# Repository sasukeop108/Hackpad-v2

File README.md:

# Hackpad-v2

Hii! This is a hackpad with 16 keys, 15 sk6812-e mini leds, a xiao rp2040 devolopment board and 16 zener diode 1n4148 with a case made using the fusion 360 software with a lid . It uses the 4*4 matrix to use less pins . The pcb was designed using the help of the pcb  software kicad. This is really basic hardware project and i have built this before but im building this once again with more keys to get back on hardware as i havent shipped any hardware project for months. It is made using the hackpad.hackclub.com guide Made for the event embassy.hackclub.com . It uses circuit python and kmk softwares.

## Schematics

## PCB

## Assembly

 ## Lid

## Case

## BOM
|Quantity|Name         |price            |purpose                       |
|--------|-------------|-----------------|------------------------------|
|1       |Xiao rp2040  |already available|for microcontrolling          |
|16      |cherry mx    |already available|the keys                      |
|16      |sk6812 mini-e|already available|rgb lights which keep changing|
|16      |blank keycaps|already available|to identify key               |
|16      |1n4148 diode |already available|to prevent ghosting of current|
|4       |M3 screws    |already available|to mount case                 |

## Building guide

First, solder the smaller components like the diodes and the sk6812 mini-e led. Then solder components like the rp2040 and switches. Download circuit python in your rp2040 and export the firmware.py code in your rp2040 storage. Assemble it in the 3d printed case available in /CAD folder. Woah! Your now good to go with a hackpad.

## Sourcing guide

Download the gerber file in the repo, paste it in any pcb fabrication service page and order your pcb! You could even change anything using the kicad files and this is fully opensource!.

## AI usage disclosure
Used AI to debug the error cause of which i was unable to push readme from vscode to repo and made it fix the issue

## Credits
- embassy.hackclub.com
- Hackpad.hackclub.com
- www.hackclub.com

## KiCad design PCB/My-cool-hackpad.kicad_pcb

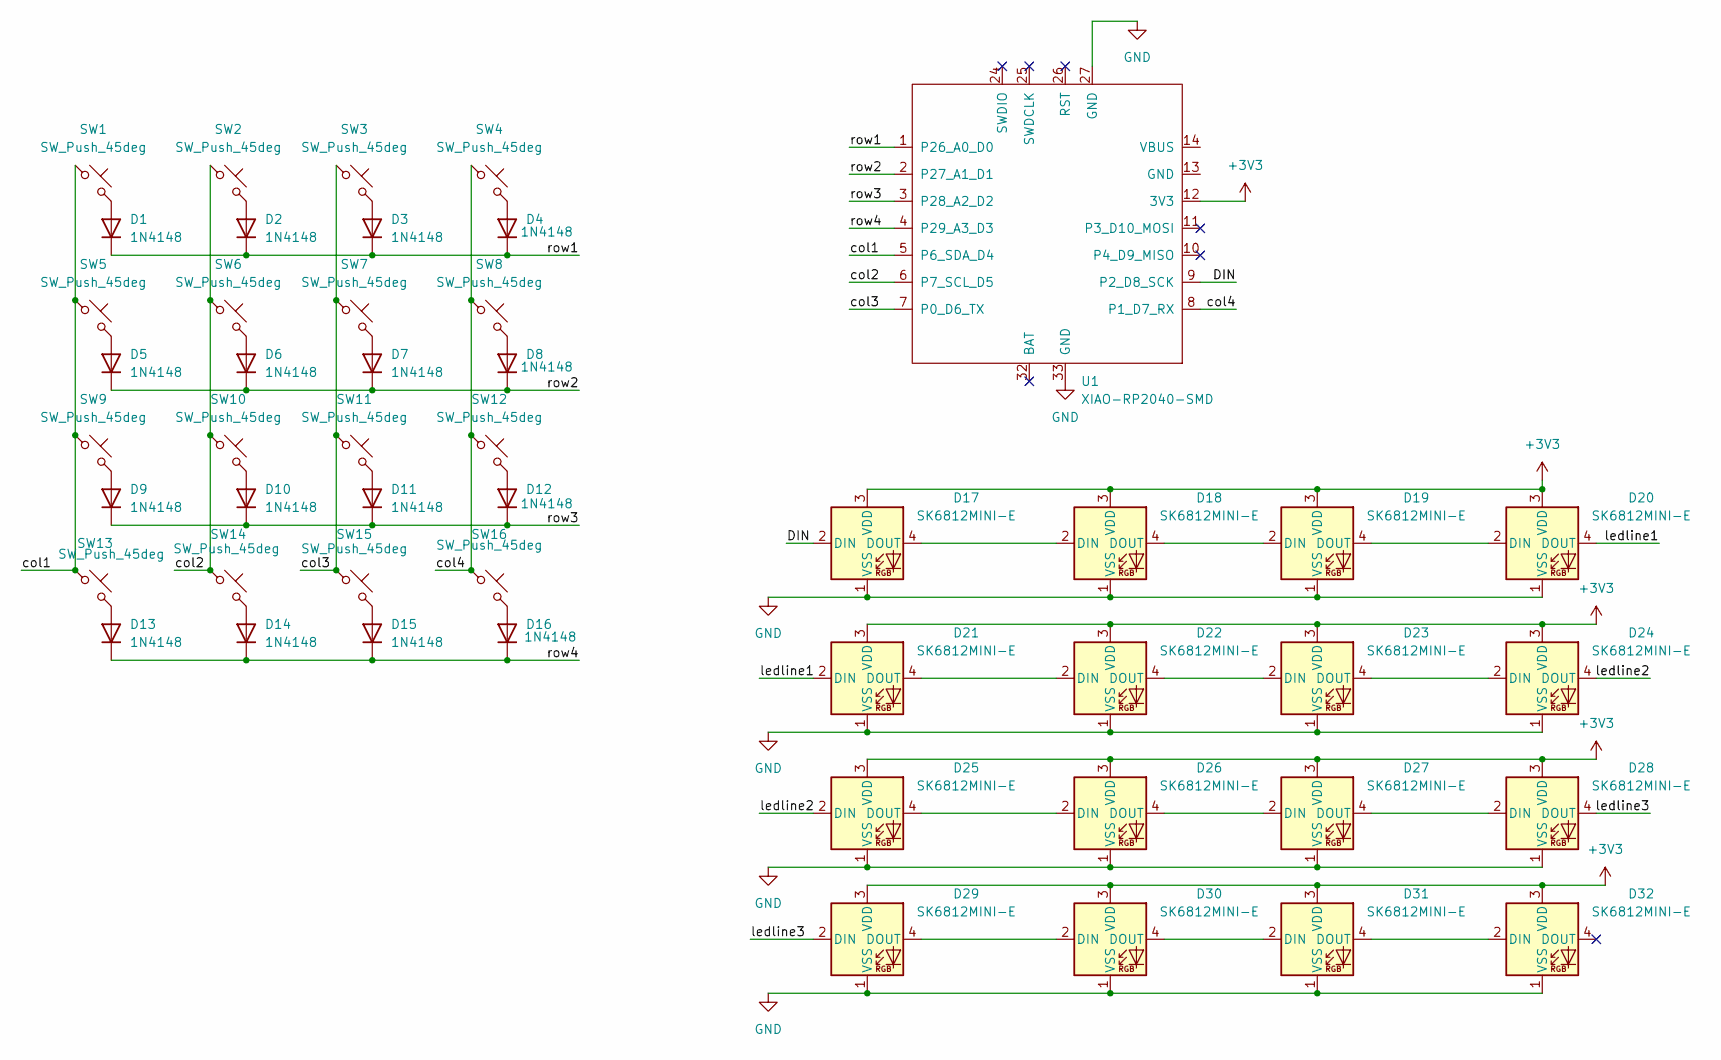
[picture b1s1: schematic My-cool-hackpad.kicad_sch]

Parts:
D1, D2, D3, D4, D5, D6, D7, D8, D9, D10, D11, D12, D13, D14, D15, D16: 1N4148; D_DO-35_SOD27_P7.62mm_Horizontal
D17, D18, D19, D20, D21, D22, D23, D24, D25, D26, D27, D28, D29, D30, D31, D32: SK6812MINI-E; LED_SK6812MINI-E_3.2x2.8mm_P1.5mm_ReverseMount
SW1, SW2, SW3, SW4, SW5, SW6, SW7, SW8, SW9, SW10, SW11, SW12, SW13, SW14, SW15, SW16: SW_Push_45deg; SW_Cherry_MX_1.00u_PCB
U1: XIAO-RP2040-SMD; XIAO-RP2040-DIP

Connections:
+3V3: D17.3 (VDD), D18.3 (VDD), D19.3 (VDD), D20.3 (VDD), D21.3 (VDD), D22.3 (VDD), D23.3 (VDD), D24.3 (VDD), D25.3 (VDD), D26.3 (VDD), D27.3 (VDD), D28.3 (VDD), D29.3 (VDD), D30.3 (VDD), D31.3 (VDD), D32.3 (VDD), U1.12 (3V3)
/DIN: D17.2 (DIN), U1.9 (P2_D8_SCK)
/col1: SW1.1, SW5.1, SW9.1, SW13.1, U1.5 (P6_SDA_D4)
/col2: SW2.1, SW6.1, SW10.1, SW14.1, U1.6 (P7_SCL_D5)
/col3: SW3.1, SW7.1, SW11.1, SW15.1, U1.7 (P0_D6_TX)
/col4: SW4.1, SW8.1, SW12.1, SW16.1, U1.8 (P1_D7_RX)
/ledline1: D20.4 (DOUT), D21.2 (DIN)
/ledline2: D24.4 (DOUT), D25.2 (DIN)
/ledline3: D28.4 (DOUT), D29.2 (DIN)
/row1: D1.1 (K), D2.1 (K), D3.1 (K), D4.1 (K), U1.1 (P26_A0_D0)
/row2: D5.1 (K), D6.1 (K), D7.1 (K), D8.1 (K), U1.2 (P27_A1_D1)
/row3: D9.1 (K), D10.1 (K), D11.1 (K), D12.1 (K), U1.3 (P28_A2_D2)
/row4: D13.1 (K), D14.1 (K), D15.1 (K), D16.1 (K), U1.4 (P29_A3_D3)
GND: D17.1 (VSS), D18.1 (VSS), D19.1 (VSS), D20.1 (VSS), D21.1 (VSS), D22.1 (VSS), D23.1 (VSS), D24.1 (VSS), D25.1 (VSS), D26.1 (VSS), D27.1 (VSS), D28.1 (VSS), D29.1 (VSS), D30.1 (VSS), D31.1 (VSS), D32.1 (VSS), U1.27 (GND), U1.33 (GND)
unnamed: D1.2 (A), SW1.2
unnamed: D2.2 (A), SW2.2
unnamed: D3.2 (A), SW3.2
unnamed: D4.2 (A), SW4.2
unnamed: D5.2 (A), SW5.2
unnamed: D6.2 (A), SW6.2
unnamed: D7.2 (A), SW7.2
unnamed: D8.2 (A), SW8.2
unnamed: D9.2 (A), SW9.2
unnamed: D10.2 (A), SW10.2
unnamed: D11.2 (A), SW11.2
unnamed: D12.2 (A), SW12.2
unnamed: D13.2 (A), SW13.2
unnamed: D14.2 (A), SW14.2
unnamed: D15.2 (A), SW15.2
unnamed: D16.2 (A), SW16.2
unnamed: D17.4 (DOUT), D18.2 (DIN)
unnamed: D18.4 (DOUT), D19.2 (DIN)
unnamed: D19.4 (DOUT), D20.2 (DIN)
unnamed: D21.4 (DOUT), D22.2 (DIN)
unnamed: D22.4 (DOUT), D23.2 (DIN)
unnamed: D23.4 (DOUT), D24.2 (DIN)
unnamed: D25.4 (DOUT), D26.2 (DIN)
unnamed: D26.4 (DOUT), D27.2 (DIN)
unnamed: D27.4 (DOUT), D28.2 (DIN)
unnamed: D29.4 (DOUT), D30.2 (DIN)
unnamed: D30.4 (DOUT), D31.2 (DIN)
unnamed: D31.4 (DOUT), D32.2 (DIN)

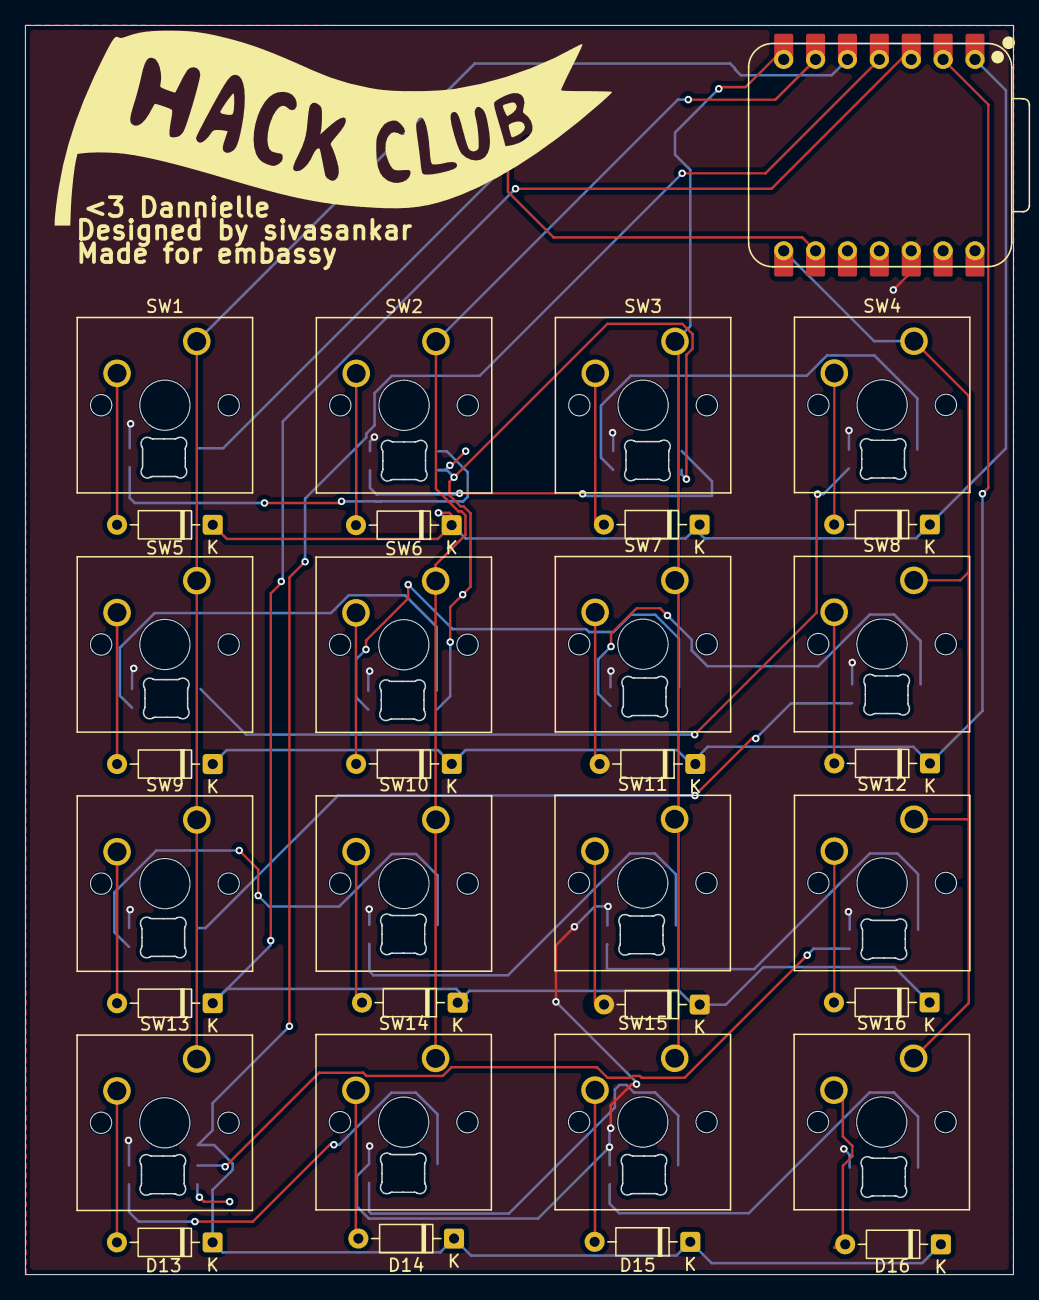
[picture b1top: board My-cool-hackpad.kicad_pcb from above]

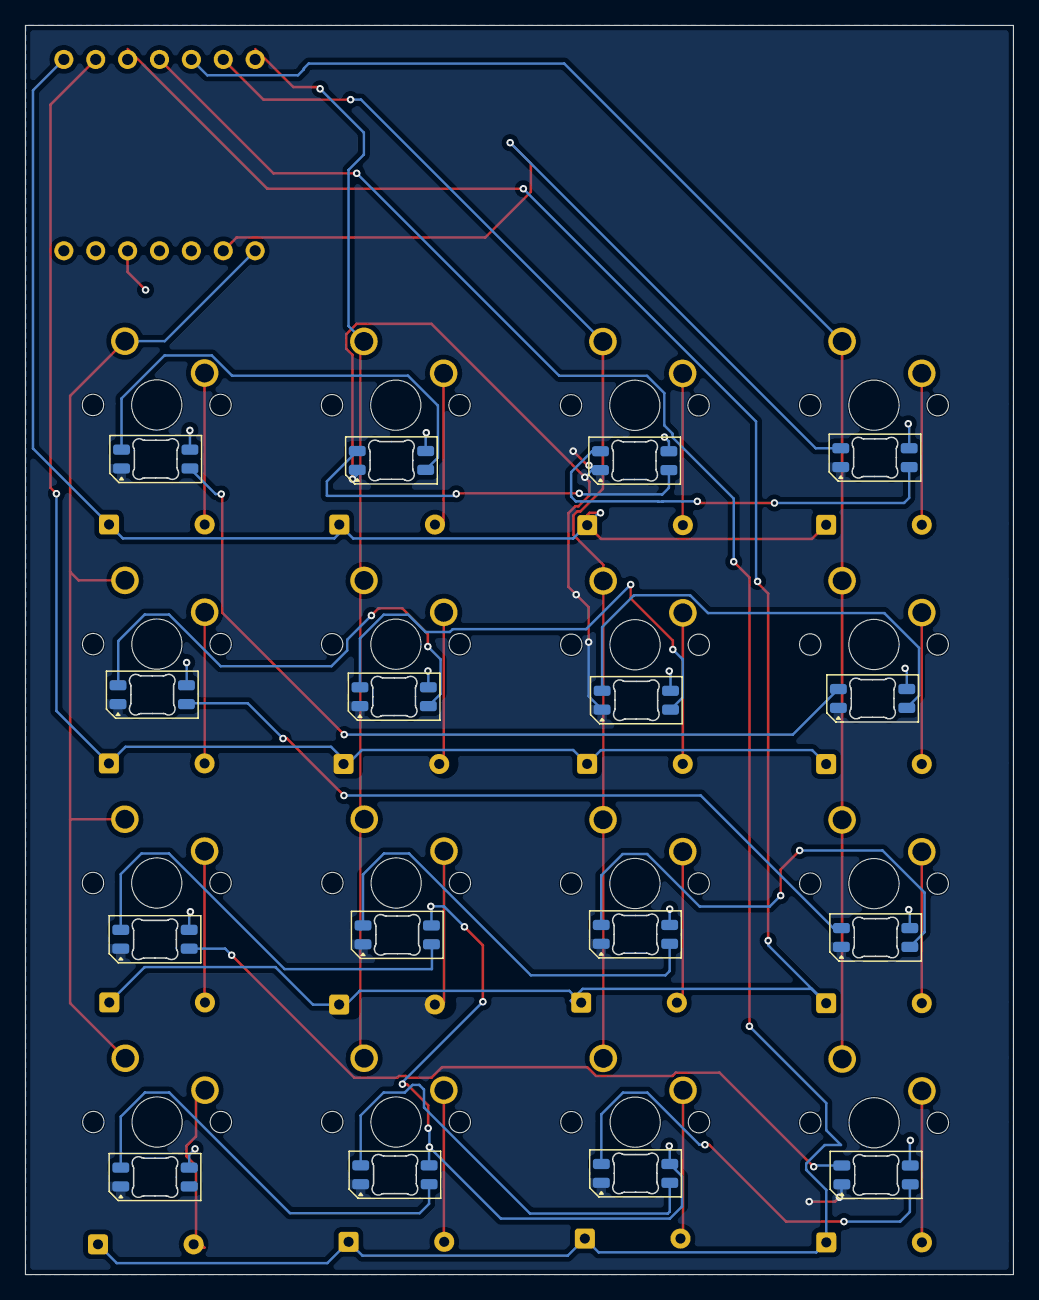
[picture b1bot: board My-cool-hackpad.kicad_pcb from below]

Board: 2 copper layers, 78.7 x 99.5 mm, 49 parts (16 on the bottom side), 42 nets.
